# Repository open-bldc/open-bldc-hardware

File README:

This project aims to create a fully open-source Brushless Drive Controller.

This repository contains all current and past hardware designs. Please refer to the open-bldc repository for the source code.

Licensing
---------
All sourcecode is licensed under GPL version 3 or later, all circuitry designs
and pcb layouts are available as original source files and licensed under
CreativeCommons BY-SA 3.0.

Feel free to use everything here as you wish! :)

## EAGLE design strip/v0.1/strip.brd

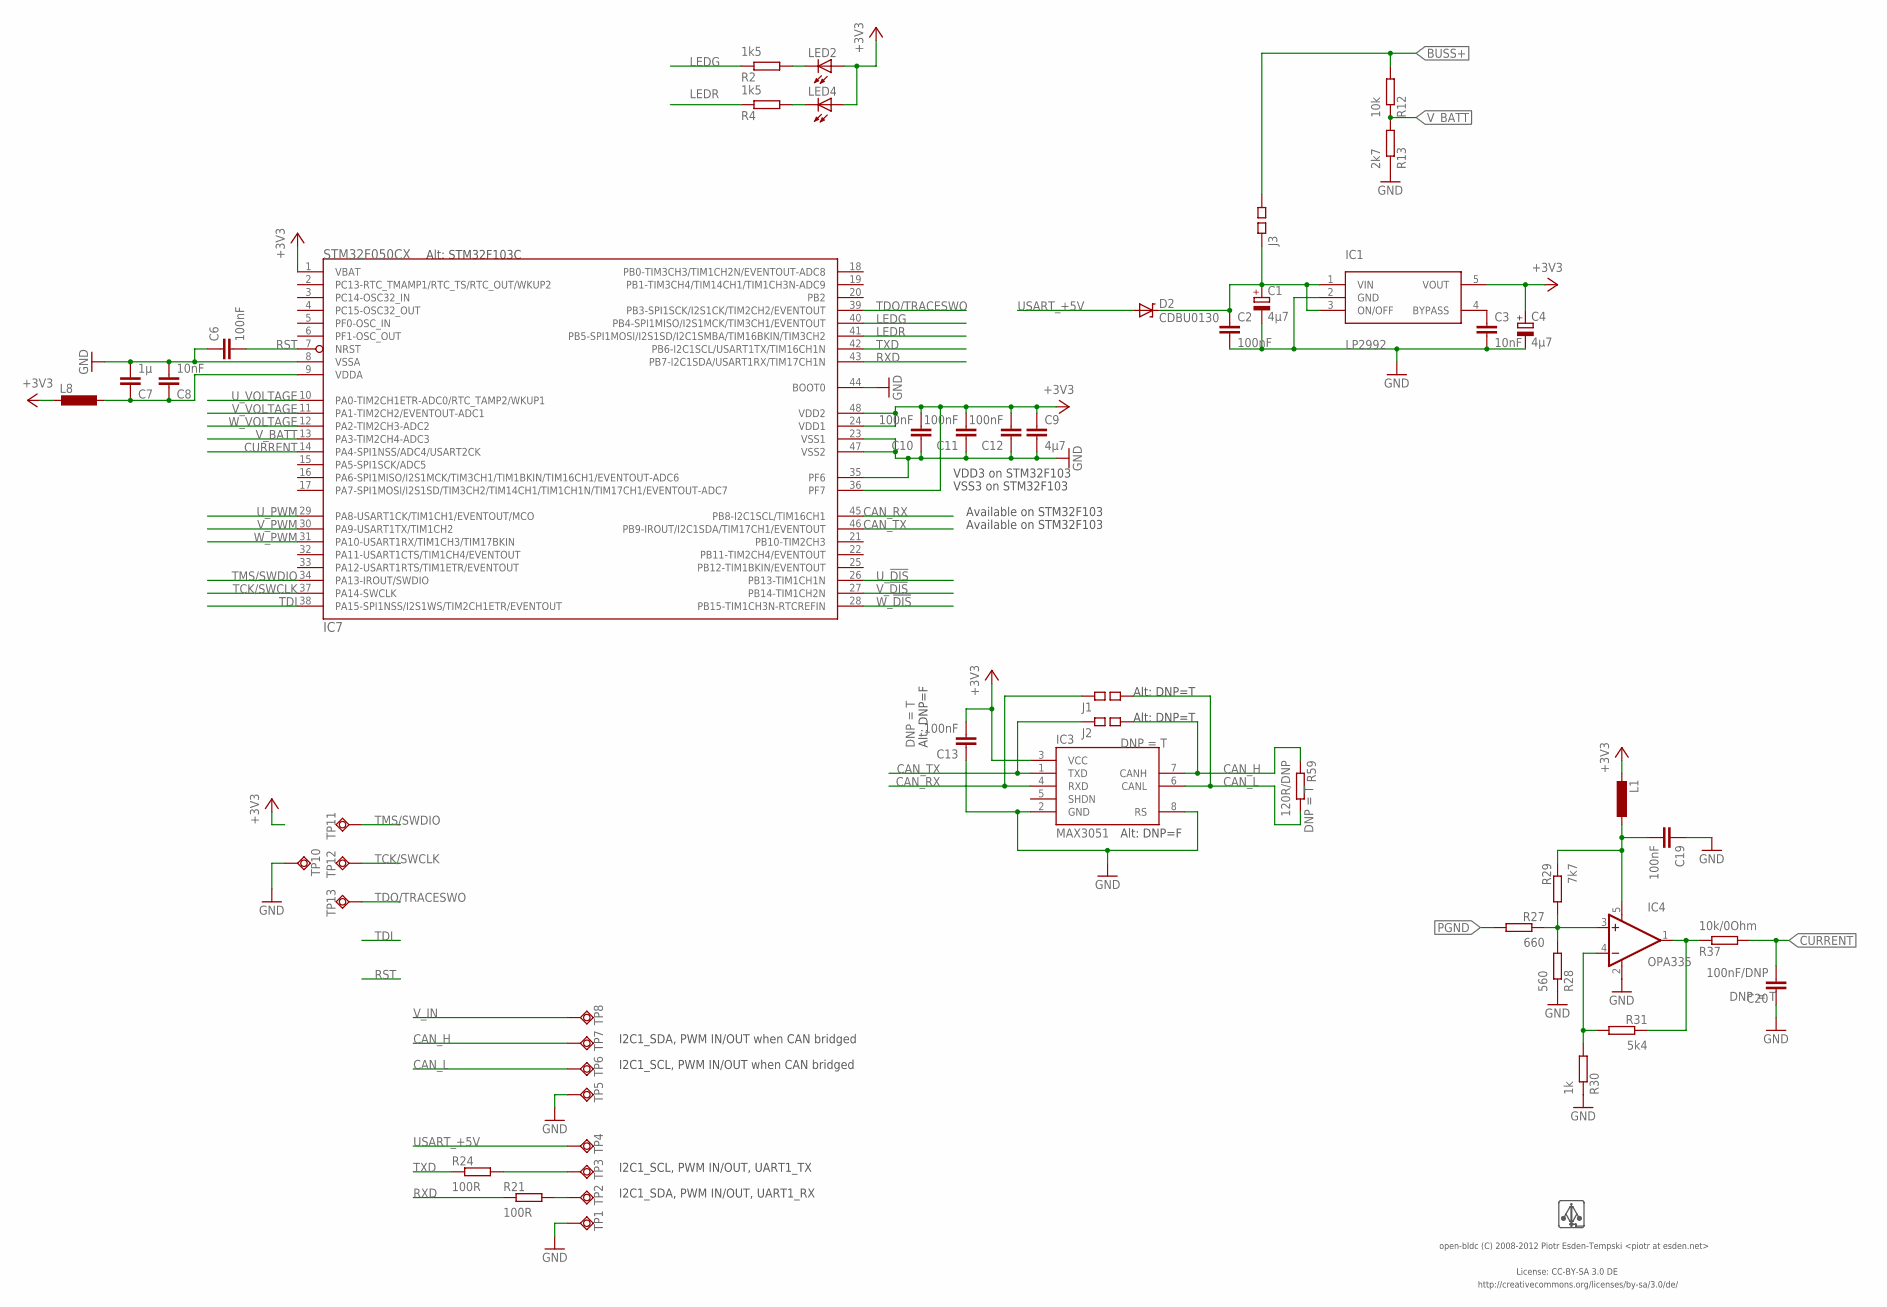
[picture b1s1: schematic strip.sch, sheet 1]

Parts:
C1, C4: 4µ7; 0805-POL-CAP; PARTNO cap-cer-0805-4u7-16v
C2, C6, C10, C11, C12, C13, C19: 100nF; 0402-CAP; PARTNO cap-cer-0402-100n
C3, C8: 10nF; 0402-CAP; PARTNO cap-cer-0402-10n
C7: 1µ; 0402-CAP; PARTNO cap-cer-0402-1u
C9: 4µ7; 0805-CAP; PARTNO cap-cer-0805-4u7
C20: 100nF/DNP; 0402-CAP; PARTNO cap-cer-0402-100n
D2: CDBU0130; 0603-DIO; PARTNO diode-0603
IC1: LP2992; SOT23-5; PARTNO vreg-sot-23-5-3v3
IC3: MAX3051; SO8; PARTNO ic-so8-can-3v3
IC4: OPA335; SOT23-5; PARTNO ic-sot-23-5-opamp
IC7: STM32F050CX; LQFP48; PARTNO mcu-lqfp-48-stm32f05
J1, J2, J3: SQ_JMP-0402; 0402-SQJMP; PARTNO res-0402-0
L1, L8: INDUCTOR-0603; 0603-IND; PARTNO ferrite-0603-600ohm
LED2: GREEN; 0402-LED; PARTNO led-0402-green
LED4: RED; 0402-LED; PARTNO led-0402-green
R2, R4: 1k5; 0402-RES; PARTNO res-0402-1k5
R12: 10k; 0402-RES; PARTNO res-0402-10k
R13: 2k7; 0402-RES; PARTNO res-0402-2k7
R21, R24: 100R; 0402-RES; PARTNO res-0402-100
R27: 660; 0402-RES; PARTNO res-0402-665
R28: 560; 0402-RES; PARTNO res-0402-560
R29: 7k7; 0402-RES; PARTNO res-0402-7k68
R30: 1k; 0402-RES; PARTNO res-0402-1k
R31: 5k4; 0402-RES; PARTNO res-0402-5k36
R37: 10k/0Ohm; 0402-RES; PARTNO res-0402-0
R59: 120R/DNP; 0402-RES; PARTNO res-0402-60.4
TP1, TP2, TP3, TP4, TP5, TP6, TP7, TP8: TPSQTP20SQ; TP20SQ; PARTNO *
TP10, TP11, TP12, TP13: TPSQTP11SQ; TP11SQ; PARTNO *
U$1: LOGO; LOGO_SILK_SMALL; PARTNO *

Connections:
+3V3: C4.+, C9.P$1 (1), C10.P$2 (2), C11.P$2 (2), C12.P$2 (2), C13.P$2 (2), IC1.5 (VOUT), IC3.3 (VCC), IC7.1 (VBAT), IC7.24 (VDD1), IC7.36 (PF7), IC7.48 (VDD2), L1.P$2 (2), L8.P$2 (2), LED2.A, LED4.A
BUSS+: J3.P$2 (2), R12.P$2 (2); also elsewhere on the board
CAN_H: IC3.7 (CANH), J2.P$2 (2), R59.P$1 (1), TP7.TP
CAN_L: IC3.6 (CANL), J1.P$2 (2), R59.P$2 (2), TP6.TP
CAN_RX: IC3.4 (RXD), IC7.45 (PB8-I2C1SCL/TIM16CH1), J1.P$1 (1)
CAN_TX: IC3.1 (TXD), IC7.46 (PB9-IROUT/I2C1SDA/TIM17CH1/EVENTOUT), J2.P$1 (1)
CURRENT: C20.P$2 (2), IC7.14 (PA4-SPI1NSS/ADC4/USART2CK), R37.P$2 (2)
CURRENT_RAW: IC4.1 (OUT), R31.P$1 (1), R37.P$1 (1)
GND: C1.-, C2.P$2 (2), C3.P$2 (2), C4.-, C6.P$1 (1), C7.P$2 (2), C8.P$2 (2), C9.P$2 (2), C10.P$1 (1), C11.P$1 (1), C12.P$1 (1), C13.P$1 (1), C19.P$1 (1), C20.P$1 (1), IC1.2 (GND), IC3.2 (GND), IC3.8 (RS), IC4.2 (V-), IC7.8 (VSSA), IC7.23 (VSS1), IC7.35 (PF6), IC7.44 (BOOT0), IC7.47 (VSS2), R13.P$1 (1), R28.P$1 (1), R30.P$1 (1), TP1.TP, TP5.TP, TP10.TP; also elsewhere on the board
LEDG: IC7.40 (PB4-SPI1MISO/I2S1MCK/TIM3CH1/EVENTOUT), R2.P$1 (1)
LEDR: IC7.41 (PB5-SPI1MOSI/I2S1SD/I2C1SMBA/TIM16BKIN/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), R4.P$1 (1)
unnamed: LED4.C, R4.P$2 (2)
unnamed: R21.P$2 (2), TP2.TP
unnamed: C19.P$2 (2), IC4.5 (V+), L1.P$1 (1), R29.P$1 (1)
unnamed: LED2.C, R2.P$2 (2)
unnamed: IC4.3 (+IN), R27.P$1 (1), R28.P$2 (2), R29.P$2 (2)
unnamed: IC4.4 (-IN), R30.P$2 (2), R31.P$2 (2)
unnamed: R24.P$2 (2), TP3.TP
unnamed: C3.P$1 (1), IC1.4 (BYPASS)
PGND: R27.P$2 (2); also elsewhere on the board
RST: C6.P$2 (2), IC7.7 (NRST)
RXD: IC7.43 (PB7-I2C1SDA/USART1RX/TIM17CH1N), R21.P$1 (1)
TCK/SWCLK: IC7.37 (PA14-SWCLK), TP12.TP
TDI: IC7.38 (PA15-SPI1NSS/I2S1WS/TIM2CH1ETR/EVENTOUT)
TDO/TRACESWO: IC7.39 (PB3-SPI1SCK/I2S1CK/TIM2CH2/EVENTOUT), TP13.TP
TMS/SWDIO: IC7.34 (PA13-IROUT/SWDIO), TP11.TP
TXD: IC7.42 (PB6-I2C1SCL/USART1TX/TIM16CH1N), R24.P$1 (1)
USART_+5V: D2.A, TP4.TP
U_!DIS: IC7.26 (PB13-TIM1CH1N); also elsewhere on the board
U_PWM: IC7.29 (PA8-USART1CK/TIM1CH1/EVENTOUT/MCO); also elsewhere on the board
U_VOLTAGE: IC7.10 (PA0-TIM2CH1ETR-ADC0/RTC_TAMP2/WKUP1); also elsewhere on the board
VDDA: C7.P$1 (1), C8.P$1 (1), IC7.9 (VDDA), L8.P$1 (1)
V_!DIS: IC7.27 (PB14-TIM1CH2N); also elsewhere on the board
V_BATT: IC7.13 (PA3-TIM2CH4-ADC3), R12.P$1 (1), R13.P$2 (2)
V_IN: C1.+, C2.P$1 (1), D2.C, IC1.1 (VIN), IC1.3 (ON/OFF), J3.P$1 (1), TP8.TP
V_PWM: IC7.30 (PA9-USART1TX/TIM1CH2); also elsewhere on the board
V_VOLTAGE: IC7.11 (PA1-TIM2CH2/EVENTOUT-ADC1); also elsewhere on the board
W_!DIS: IC7.28 (PB15-TIM1CH3N-RTCREFIN); also elsewhere on the board
W_PWM: IC7.31 (PA10-USART1RX/TIM1CH3/TIM17BKIN); also elsewhere on the board
W_VOLTAGE: IC7.12 (PA2-TIM2CH3-ADC2); also elsewhere on the board

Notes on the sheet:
License: CC-BY-SA 3.0 DE
http://creativecommons.org/licenses/by-sa/3.0/de/
open-bldc (C) 2008-2012 Piotr Esden-Tempski <piotr at esden.net>
VDD3 on STM32F103
VSS3 on STM32F103
Available on STM32F103
Alt: STM32F103C
Alt: DNP=T
Alt: DNP=F
I2C1_SDA, PWM IN/OUT when CAN bridged
I2C1_SCL, PWM IN/OUT when CAN bridged
I2C1_SCL, PWM IN/OUT, UART1_TX
I2C1_SDA, PWM IN/OUT, UART1_RX

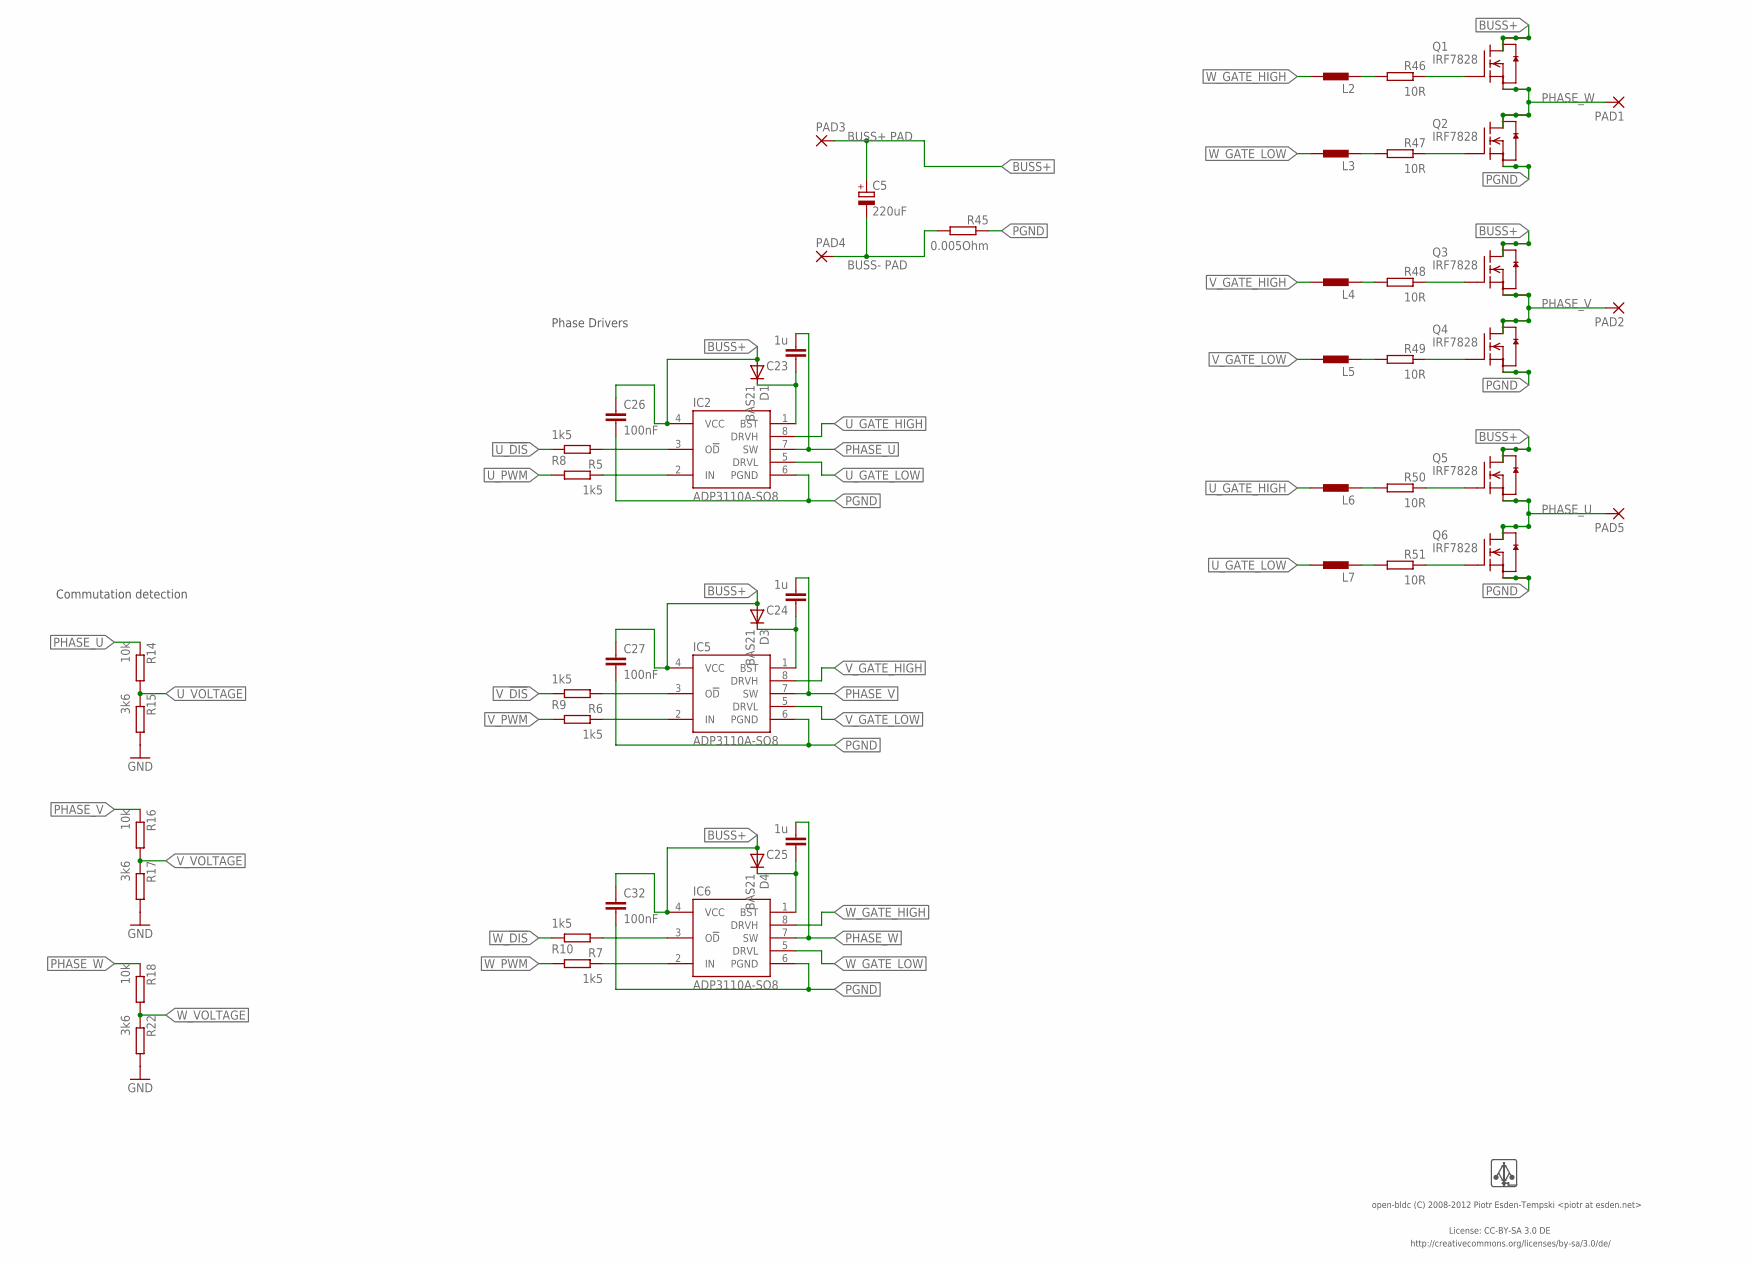
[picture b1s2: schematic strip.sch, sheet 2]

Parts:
C5: 220uF; 7343/D; PARTNO cap-tan-D-220u-16v
C23, C24, C25: 1u; 0603-CAP; PARTNO cap-tan-0603-1u
C26, C27, C32: 100nF; 0402-CAP; PARTNO cap-cer-0402-100n
D1, D3, D4: BAS21; SOD-123-DIO; PARTNO diode-sod-123
IC2, IC5, IC6: ADP3110A-SO8; SO8; PARTNO ic-so8-mosfet-driver-buck
L2, L3, L4, L5, L6, L7: INDUCTOR-0402; 0402-IND; PARTNO res-0402-0
PAD1, PAD2, PAD3, PAD4, PAD5: SMD5; SMD2,54-5,08; PARTNO *
Q1, Q2, Q3, Q4, Q5, Q6: IRF7828; SO8; PARTNO ic-so8-mosfet-n-ch-30v-15a
R5, R6, R7, R8, R9, R10: 1k5; 0402-RES; PARTNO res-0402-1k5
R14, R16, R18: 10k; 0402-RES; PARTNO res-0402-10k
R15, R17, R22: 3k6; 0402-RES; PARTNO res-0402-3k6
R45: 0.005Ohm; 1206-RES; PARTNO res-1206-0005
R46, R47, R48, R49, R50, R51: 10R; 0402-RES; PARTNO res-0402-10
U$2: LOGO; LOGO_SILK_SMALL; PARTNO *

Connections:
BUSS+: C5.+, C26.P$1 (1), C27.P$1 (1), C32.P$1 (1), D1.A, D3.A, D4.A, IC2.4 (VCC), IC5.4 (VCC), IC6.4 (VCC), PAD3.1, Q1.5 (D1), Q1.6 (D2), Q1.7 (D3), Q1.8 (D4), Q3.5 (D1), Q3.6 (D2), Q3.7 (D3), Q3.8 (D4), Q5.5 (D1), Q5.6 (D2), Q5.7 (D3), Q5.8 (D4); also elsewhere on the board
GND: C5.-, PAD4.1, R15.P$2 (2), R17.P$2 (2), R22.P$2 (2), R45.P$2 (2); also elsewhere on the board
unnamed: C23.P$1 (1), D1.C, IC2.1 (BST)
unnamed: C24.P$1 (1), D3.C, IC5.1 (BST)
unnamed: C25.P$1 (1), D4.C, IC6.1 (BST)
unnamed: L2.P$2 (2), R46.P$2 (2)
unnamed: L3.P$2 (2), R47.P$2 (2)
unnamed: L4.P$2 (2), R48.P$2 (2)
unnamed: L5.P$2 (2), R49.P$2 (2)
unnamed: L6.P$2 (2), R50.P$2 (2)
unnamed: L7.P$2 (2), R51.P$2 (2)
unnamed: Q1.4 (G), R46.P$1 (1)
unnamed: Q2.4 (G), R47.P$1 (1)
unnamed: Q3.4 (G), R48.P$1 (1)
unnamed: Q4.4 (G), R49.P$1 (1)
unnamed: Q5.4 (G), R50.P$1 (1)
unnamed: Q6.4 (G), R51.P$1 (1)
PGND: C26.P$2 (2), C27.P$2 (2), C32.P$2 (2), IC2.6 (PGND), IC5.6 (PGND), IC6.6 (PGND), Q2.1 (S3), Q2.2 (S2), Q2.3 (S1), Q4.1 (S3), Q4.2 (S2), Q4.3 (S1), Q6.1 (S3), Q6.2 (S2), Q6.3 (S1), R45.P$1 (1); also elsewhere on the board
PHASE_U: C23.P$2 (2), IC2.7 (SW), PAD5.1, Q5.1 (S3), Q5.2 (S2), Q5.3 (S1), Q6.5 (D1), Q6.6 (D2), Q6.7 (D3), Q6.8 (D4), R14.P$1 (1)
PHASE_V: C24.P$2 (2), IC5.7 (SW), PAD2.1, Q3.1 (S3), Q3.2 (S2), Q3.3 (S1), Q4.5 (D1), Q4.6 (D2), Q4.7 (D3), Q4.8 (D4), R16.P$1 (1)
PHASE_W: C25.P$2 (2), IC6.7 (SW), PAD1.1, Q1.1 (S3), Q1.2 (S2), Q1.3 (S1), Q2.5 (D1), Q2.6 (D2), Q2.7 (D3), Q2.8 (D4), R18.P$1 (1)
U_!DIS: R8.P$1 (1); also elsewhere on the board
U_!DIS!1: IC2.3 (O!D), R8.P$2 (2)
U_GATE_HIGH: IC2.8 (DRVH), L6.P$1 (1)
U_GATE_LOW: IC2.5 (DRVL), L7.P$1 (1)
U_PWM: R5.P$2 (2); also elsewhere on the board
U_PWM1: IC2.2 (IN), R5.P$1 (1)
U_VOLTAGE: R14.P$2 (2), R15.P$1 (1); also elsewhere on the board
V_!DIS: R9.P$1 (1); also elsewhere on the board
V_!DIS!1: IC5.3 (O!D), R9.P$2 (2)
V_GATE_HIGH: IC5.8 (DRVH), L4.P$1 (1)
V_GATE_LOW: IC5.5 (DRVL), L5.P$1 (1)
V_PWM: R6.P$2 (2); also elsewhere on the board
V_PWM1: IC5.2 (IN), R6.P$1 (1)
V_VOLTAGE: R16.P$2 (2), R17.P$1 (1); also elsewhere on the board
W_!DIS: R10.P$1 (1); also elsewhere on the board
W_!DIS1: IC6.3 (O!D), R10.P$2 (2)
W_GATE_HIGH: IC6.8 (DRVH), L2.P$1 (1)
W_GATE_LOW: IC6.5 (DRVL), L3.P$1 (1)
W_PWM: R7.P$2 (2); also elsewhere on the board
W_PWM1: IC6.2 (IN), R7.P$1 (1)
W_VOLTAGE: R18.P$2 (2), R22.P$1 (1); also elsewhere on the board

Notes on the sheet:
Phase Drivers
Commutation detection
BUSS+ PAD
BUSS- PAD
License: CC-BY-SA 3.0 DE
http://creativecommons.org/licenses/by-sa/3.0/de/
open-bldc (C) 2008-2012 Piotr Esden-Tempski <piotr at esden.net>

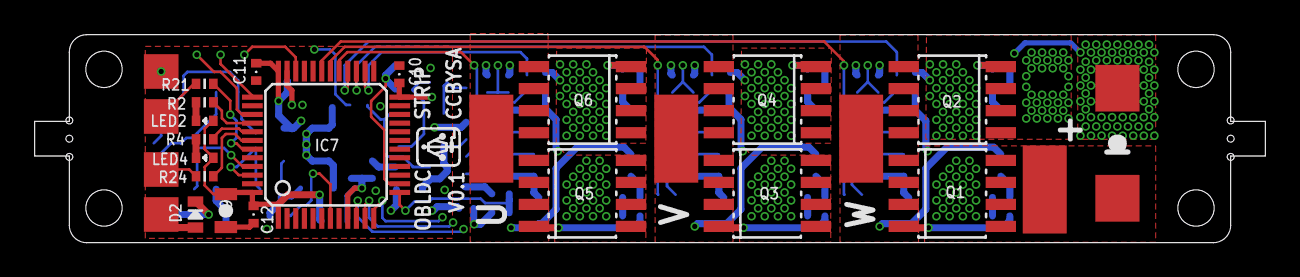
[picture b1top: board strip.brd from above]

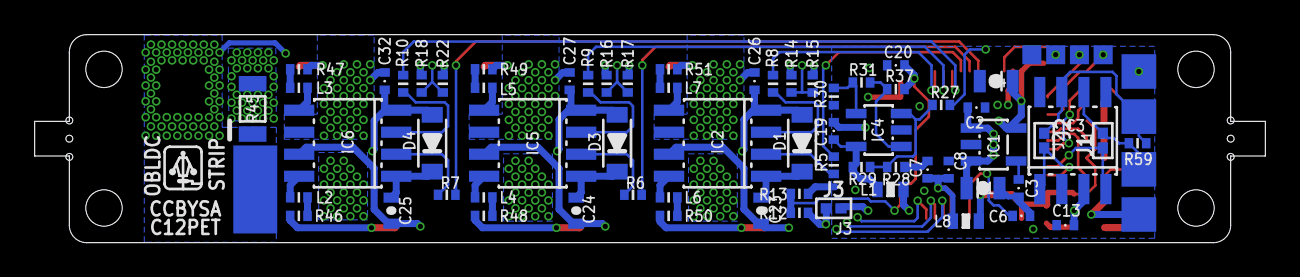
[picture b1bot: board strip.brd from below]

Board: 4 copper layers, 71.0 x 12.0 mm, 102 parts (74 on the bottom side), 69 nets.

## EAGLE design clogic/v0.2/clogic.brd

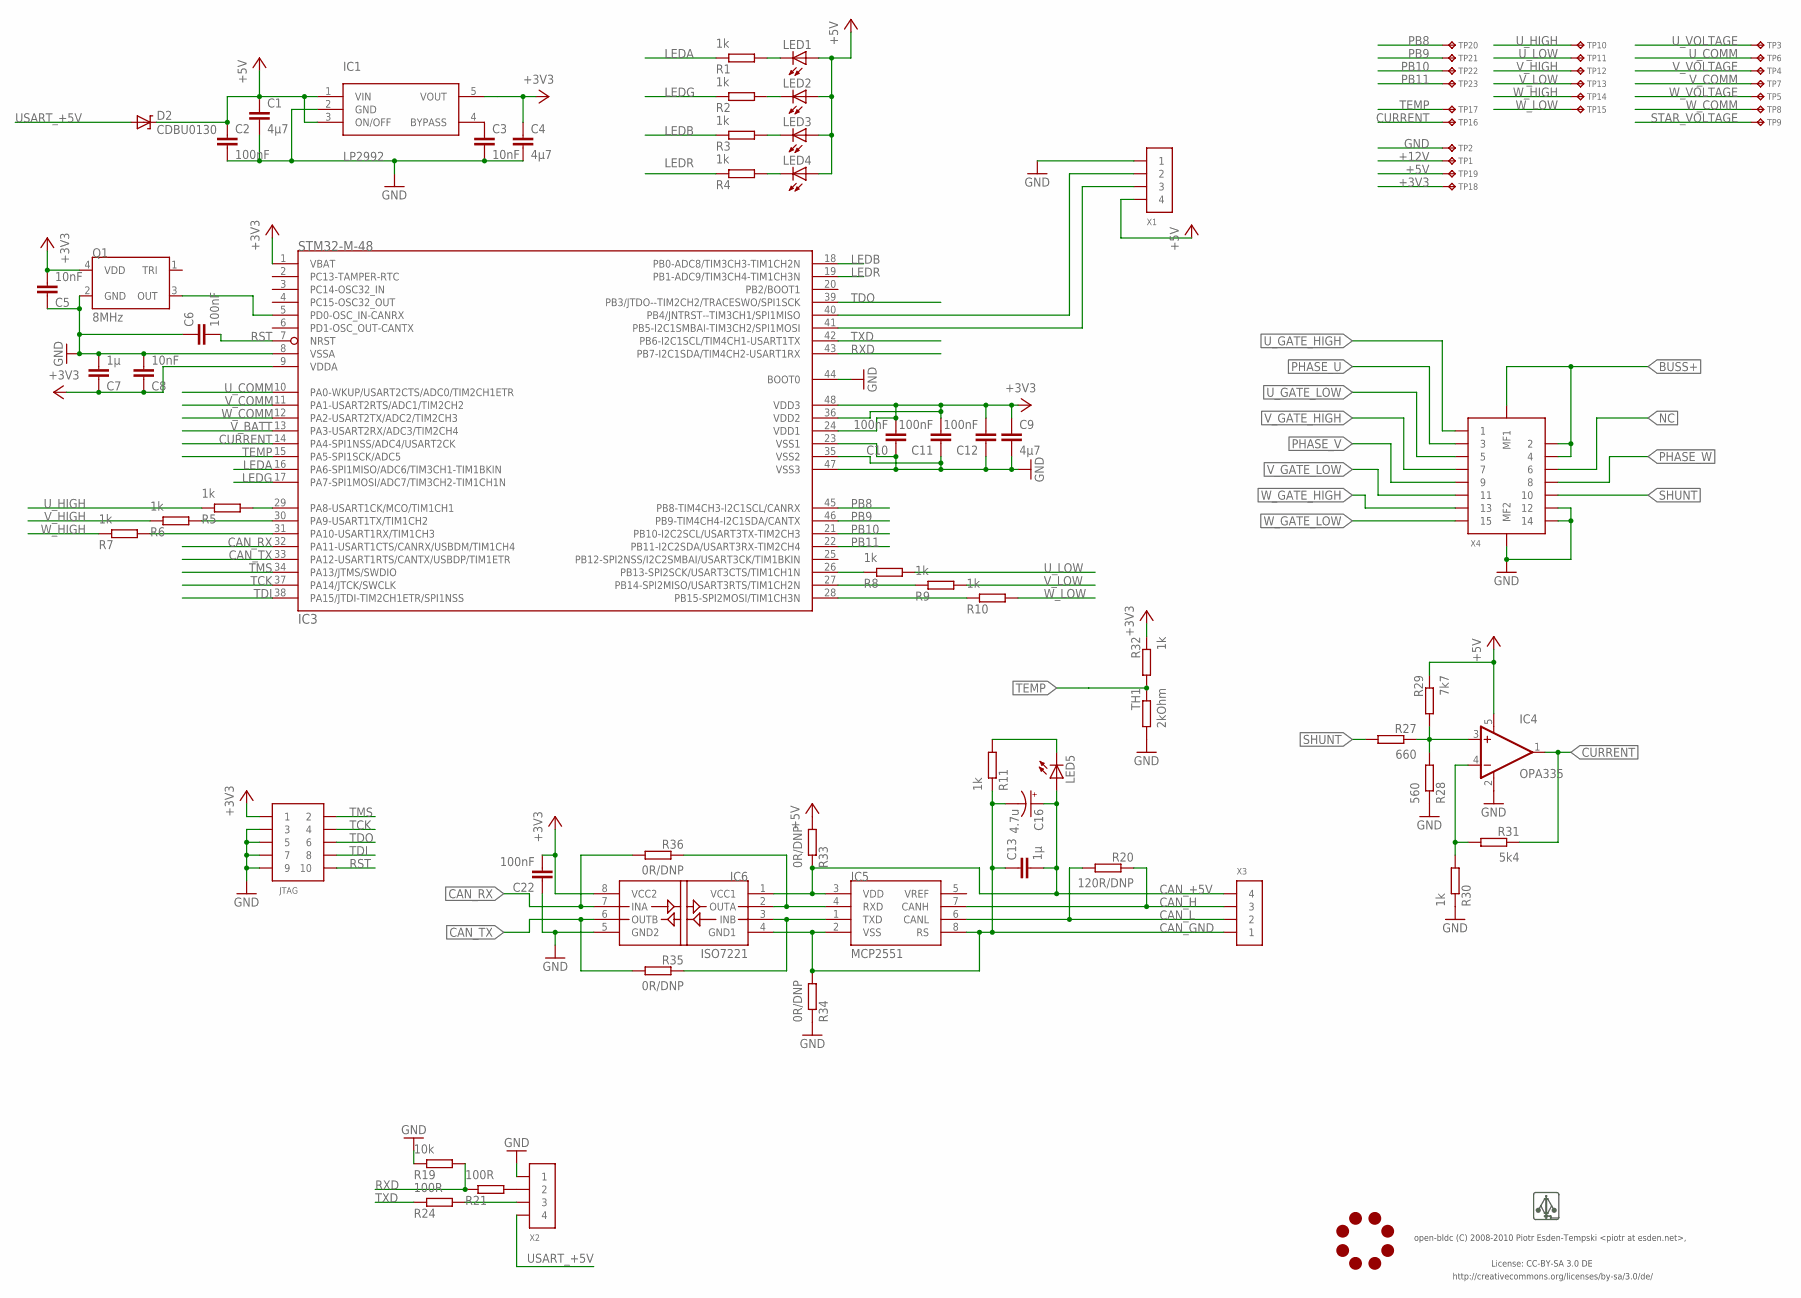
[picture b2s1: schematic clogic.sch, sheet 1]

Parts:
C1, C4, C9: 4µ7; 0603-CAP
C2, C6, C10, C11, C12, C22: 100nF; 0603-CAP
C3, C5, C8: 10nF; 0603-CAP
C7, C13: 1µ; 0603-CAP
C16: 4.7u; CAP_0805TANT_F95
D2: CDBU0130; 0603-LED
IC1: LP2992; SOT23-5
IC3: STM32-M-48; LQFP48
IC4: OPA335; SOT23-5
IC5: MCP2551; SO8
IC6: ISO7221; SO8
JL1: JOBY_LOGO-6MIL; JOBY_LOGO_6MIL
JTAG: CONN_5-2-FTSH-V; FTSH-105-DV
LED1: AMBER; 0603-LED
LED2: GREEN; 0603-LED
LED3: BLUE; 0603-LED
LED4: RED; 0603-LED
LED5: WHITE; 0603-LED
Q1: 8MHz; ASE_OSCILLATOR
R1, R2, R3, R4, R5, R6, R7, R8, R9, R10, R11, R30, R32: 1k; 0603-RES
R19: 10k; 0603-RES
R20: 120R/DNP; 0603-RES
R21, R24: 100R; 0603-RES
R27: 660; 0603-RES
R28: 560; 0603-RES
R29: 7k7; 0603-RES
R31: 5k4; 0603-RES
R33, R34, R35, R36: 0R/DNP; 0603-RES
TH1: 2kOhm; 0603-RES
TP1, TP2, TP3, TP4, TP5, TP6, TP7, TP8, TP9, TP10, TP11, TP12, TP13, TP14, TP15, TP16, TP17, TP18, TP19, TP20, TP21, TP22, TP23: TP-09RSMD; TP09R
U$1: LOGO
X1, X2, X3: CONN_4-1-53261; PB-53261-04
X4: CONN_15-2-2MT-DF9; DF9-15

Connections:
+3V3: C4.P$1 (1), C5.P$2 (2), C7.P$1 (1), C8.P$1 (1), C9.P$1 (1), C10.P$2 (2), C11.P$2 (2), C12.P$2 (2), C22.P$2 (2), IC1.5 (VOUT), IC3.1 (VBAT), IC3.9 (VDDA), IC3.24 (VDD1), IC3.36 (VDD2), IC3.48 (VDD3), IC6.8 (VCC2), JTAG.1, Q1.4 (VDD), R32.P$1 (1), TP18.P$1
+5V: C1.P$1 (1), C2.P$1 (1), D2.C, IC1.1 (VIN), IC1.3 (ON/OFF), IC4.5 (V+), LED1.A, LED2.A, LED3.A, LED4.A, R29.P$1 (1), R33.P$2 (2), TP19.P$1, X1.4; also elsewhere on the board
+12V: TP1.P$1; also elsewhere on the board
A: IC3.40 (PB4/JNTRST--TIM3CH1/SPI1MISO), X1.2
B: IC3.41 (PB5-I2C1SMBAI-TIM3CH2/SPI1MOSI), X1.3
BUSS+: X4.2, X4.4, X4.MF1; also elsewhere on the board
CAN_+5V: C13.P$2 (2), C16.P$1 (+), IC5.3 (VDD), IC6.1 (VCC1), LED5.A, R33.P$1 (1), X3.4
CAN_GND: C13.P$1 (1), C16.P$2 (-), IC5.2 (VSS), IC5.8 (RS), IC6.4 (GND1), R11.P$1 (1), R34.P$2 (2), X3.1
CAN_H: IC5.7 (CANH), R20.P$1 (1), X3.3
CAN_L: IC5.6 (CANL), R20.P$2 (2), X3.2
CAN_RX: IC3.32 (PA11-USART1CTS/CANRX/USBDM/TIM1CH4), IC6.7 (INA), R36.P$2 (2)
CAN_TX: IC3.33 (PA12-USART1RTS/CANTX/USBDP/TIM1ETR), IC6.6 (OUTB), R35.P$2 (2)
CURRENT: IC3.14 (PA4-SPI1NSS/ADC4/USART2CK), IC4.1 (OUT), R31.P$1 (1), TP16.P$1
GND: C1.P$2 (2), C2.P$2 (2), C3.P$2 (2), C4.P$2 (2), C5.P$1 (1), C6.P$1 (1), C7.P$2 (2), C8.P$2 (2), C9.P$2 (2), C10.P$1 (1), C11.P$1 (1), C12.P$1 (1), C22.P$1 (1), IC1.2 (GND), IC3.8 (VSSA), IC3.23 (VSS1), IC3.35 (VSS2), IC3.44 (BOOT0), IC3.47 (VSS3), IC4.2 (V-), IC6.5 (GND2), JTAG.3, JTAG.5, JTAG.7, JTAG.9, Q1.2 (GND), R19.P$1 (1), R28.P$1 (1), R30.P$1 (1), R34.P$1 (1), TH1.P$2 (2), TP2.P$1, X1.1, X2.1, X4.12, X4.14, X4.MF2; also elsewhere on the board
LEDA: IC3.16 (PA6-SPI1MISO/ADC6/TIM3CH1-TIM1BKIN), R1.P$1 (1)
LEDB: IC3.18 (PB0-ADC8/TIM3CH3-TIM1CH2N), R3.P$1 (1)
LEDG: IC3.17 (PA7-SPI1MOSI/ADC7/TIM3CH2-TIM1CH1N), R2.P$1 (1)
LEDR: IC3.19 (PB1-ADC9/TIM3CH4-TIM1CH3N), R4.P$1 (1)
unnamed: LED5.C, R11.P$2 (2)
unnamed: LED1.C, R1.P$2 (2)
unnamed: LED4.C, R4.P$2 (2)
unnamed: LED3.C, R3.P$2 (2)
unnamed: R21.P$2 (2), X2.2
unnamed: LED2.C, R2.P$2 (2)
unnamed: IC4.3 (+IN), R27.P$1 (1), R28.P$2 (2), R29.P$2 (2)
unnamed: IC4.4 (-IN), R30.P$2 (2), R31.P$2 (2)
unnamed: IC5.1 (TXD), IC6.3 (INB), R35.P$1 (1)
unnamed: IC5.4 (RXD), IC6.2 (OUTA), R36.P$1 (1)
unnamed: R24.P$2 (2), X2.3
unnamed: C3.P$1 (1), IC1.4 (BYPASS)
unnamed: IC3.26 (PB13-SPI2SCK/USART3CTS/TIM1CH1N), R8.P$1 (1)
unnamed: IC3.27 (PB14-SPI2MISO/USART3RTS/TIM1CH2N), R9.P$1 (1)
unnamed: IC3.28 (PB15-SPI2MOSI/TIM1CH3N), R10.P$1 (1)
unnamed: IC3.5 (PD0-OSC_IN-CANRX), Q1.3 (OUT)
unnamed: IC3.29 (PA8-USART1CK/MCO/TIM1CH1), R5.P$2 (2)
unnamed: IC3.30 (PA9-USART1TX/TIM1CH2), R6.P$2 (2)
unnamed: IC3.31 (PA10-USART1RX/TIM1CH3), R7.P$2 (2)
NC: X4.6
PB8: IC3.45 (PB8-TIM4CH3-I2C1SCL/CANRX), TP20.P$1
PB9: IC3.46 (PB9-TIM4CH4-I2C1SDA/CANTX), TP21.P$1
PB10: IC3.21 (PB10-I2C2SCL/USART3TX-TIM2CH3), TP22.P$1
PB11: IC3.22 (PB11-I2C2SDA/USART3RX-TIM2CH4), TP23.P$1
PHASE_U: X4.3; also elsewhere on the board
PHASE_V: X4.9; also elsewhere on the board
PHASE_W: X4.8; also elsewhere on the board
RST: C6.P$2 (2), IC3.7 (NRST), JTAG.10
RXD: IC3.43 (PB7-I2C1SDA/TIM4CH2-USART1RX), R19.P$2 (2), R21.P$1 (1)
SHUNT: R27.P$2 (2), X4.10
STAR_VOLTAGE: TP9.P$1; also elsewhere on the board
TCK: IC3.37 (PA14/JTCK/SWCLK), JTAG.4
TDI: IC3.38 (PA15/JTDI-TIM2CH1ETR/SPI1NSS), JTAG.8
TDO: IC3.39 (PB3/JTDO--TIM2CH2/TRACESWO/SPI1SCK), JTAG.6
TEMP: IC3.15 (PA5-SPI1SCK/ADC5), R32.P$2 (2), TH1.P$1 (1), TP17.P$1
TMS: IC3.34 (PA13/JTMS/SWDIO), JTAG.2
TXD: IC3.42 (PB6-I2C1SCL/TIM4CH1-USART1TX), R24.P$1 (1)
USART_+5V: D2.A, X2.4
U_COMM: IC3.10 (PA0-WKUP/USART2CTS/ADC0/TIM2CH1ETR), TP6.P$1; also elsewhere on the board
U_GATE_HIGH: X4.1; also elsewhere on the board
U_GATE_LOW: X4.5; also elsewhere on the board
U_HIGH: R5.P$1 (1), TP10.P$1; also elsewhere on the board
U_LOW: R8.P$2 (2), TP11.P$1; also elsewhere on the board
U_VOLTAGE: TP3.P$1; also elsewhere on the board
V_BATT: IC3.13 (PA3-USART2RX/ADC3/TIM2CH4); also elsewhere on the board
V_COMM: IC3.11 (PA1-USART2RTS/ADC1/TIM2CH2), TP7.P$1; also elsewhere on the board
V_GATE_HIGH: X4.7; also elsewhere on the board
V_GATE_LOW: X4.11; also elsewhere on the board
V_HIGH: R6.P$1 (1), TP12.P$1; also elsewhere on the board
V_LOW: R9.P$2 (2), TP13.P$1; also elsewhere on the board
V_VOLTAGE: TP4.P$1; also elsewhere on the board
W_COMM: IC3.12 (PA2-USART2TX/ADC2/TIM2CH3), TP8.P$1; also elsewhere on the board
W_GATE_HIGH: X4.13; also elsewhere on the board
W_GATE_LOW: X4.15; also elsewhere on the board
W_HIGH: R7.P$1 (1), TP14.P$1; also elsewhere on the board
W_LOW: R10.P$2 (2), TP15.P$1; also elsewhere on the board
W_VOLTAGE: TP5.P$1; also elsewhere on the board

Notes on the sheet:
License: CC-BY-SA 3.0 DE
http://creativecommons.org/licenses/by-sa/3.0/de/
open-bldc (C) 2008-2010 Piotr Esden-Tempski <piotr at esden.net>,

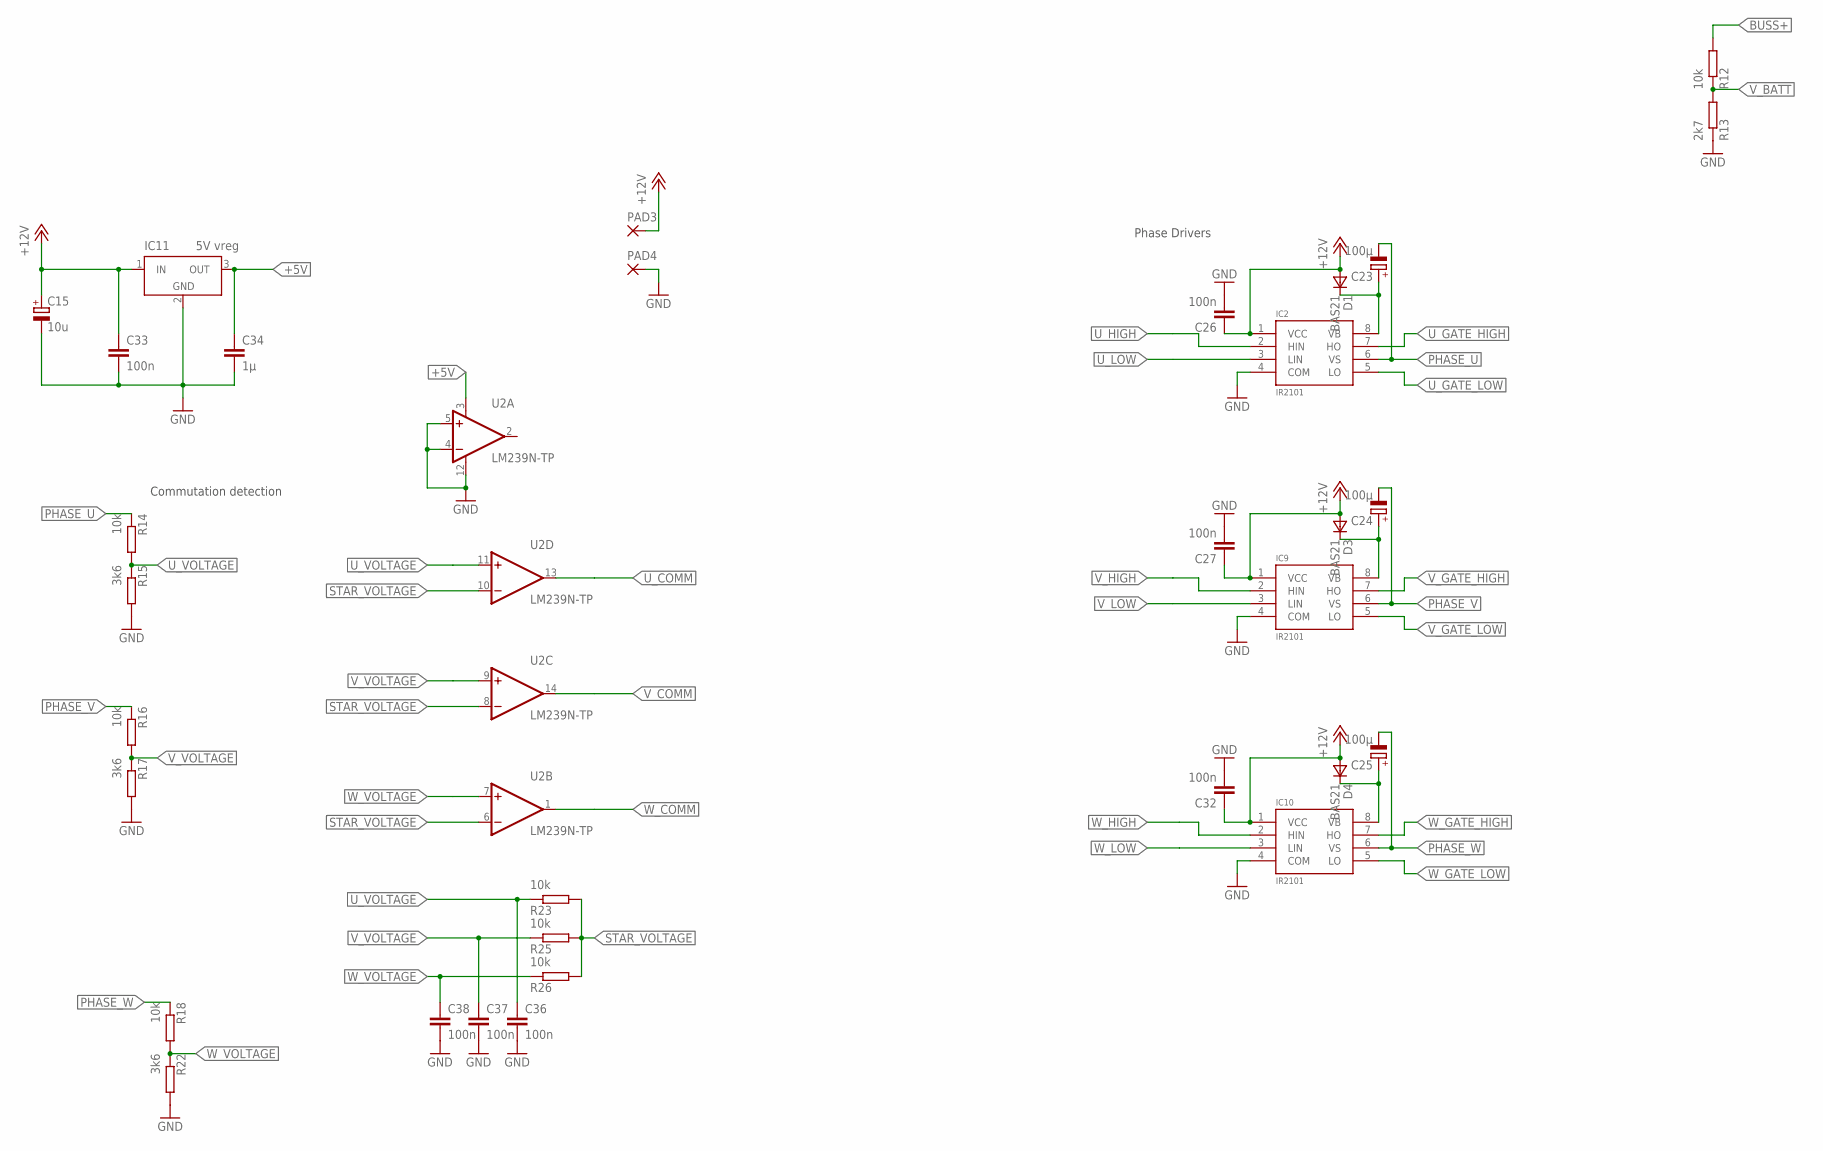
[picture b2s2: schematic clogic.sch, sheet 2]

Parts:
C15: 10u; 3528/B
C23, C24, C25: 100µ; 0805-POL-CAP
C26, C27, C32, C33, C36, C37, C38: 100n; 0603-CAP
C34: 1µ; 0603-CAP
D1, D3, D4: BAS21; SOT-23
IC2, IC9, IC10: IR2101; SO-8
IC11: 5V vreg; SOT223
PAD3, PAD4: SMD5; SMD2,54-5,08
R12, R14, R16, R18, R23, R25, R26: 10k; 0603-RES
R13: 2k7; 0603-RES
R15, R17, R22: 3k6; 0603-RES
U2: LM239N-TP; TSSOP_14

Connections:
+5V: C34.P$1 (1), IC11.3 (OUT), U2.3 (V+); also elsewhere on the board
+12V: C15.+, C26.P$1 (1), C27.P$1 (1), C32.P$1 (1), C33.P$1 (1), D1.3 (A), D3.3 (A), D4.3 (A), IC2.1 (VCC), IC9.1 (VCC), IC10.1 (VCC), IC11.1 (IN), PAD3.1; also elsewhere on the board
BUSS+: R12.P$2 (2); also elsewhere on the board
GND: C15.-, C26.P$2 (2), C27.P$2 (2), C32.P$2 (2), C33.P$2 (2), C34.P$2 (2), C36.P$2 (2), C37.P$2 (2), C38.P$2 (2), IC2.4 (COM), IC9.4 (COM), IC10.4 (COM), IC11.2 (GND), IC11.4 (GND), PAD4.1, R13.P$1 (1), R15.P$2 (2), R17.P$2 (2), R22.P$2 (2), U2.4 (-IN), U2.5 (+IN), U2.12 (V-); also elsewhere on the board
unnamed: C23.+, D1.1 (C), IC2.8 (VB)
unnamed: C24.+, D3.1 (C), IC9.8 (VB)
unnamed: C25.+, D4.1 (C), IC10.8 (VB)
PHASE_U: C23.-, IC2.6 (VS), R14.P$1 (1); also elsewhere on the board
PHASE_V: C24.-, IC9.6 (VS), R16.P$1 (1); also elsewhere on the board
PHASE_W: C25.-, IC10.6 (VS), R18.P$1 (1); also elsewhere on the board
STAR_VOLTAGE: R23.P$2 (2), R25.P$2 (2), R26.P$2 (2), U2.6 (-IN), U2.8 (-IN), U2.10 (-IN); also elsewhere on the board
U_COMM: U2.13 (OUT); also elsewhere on the board
U_GATE_HIGH: IC2.7 (HO); also elsewhere on the board
U_GATE_LOW: IC2.5 (LO); also elsewhere on the board
U_HIGH: IC2.2 (HIN); also elsewhere on the board
U_LOW: IC2.3 (LIN); also elsewhere on the board
U_VOLTAGE: C36.P$1 (1), R14.P$2 (2), R15.P$1 (1), R23.P$1 (1), U2.11 (+IN); also elsewhere on the board
V_BATT: R12.P$1 (1), R13.P$2 (2); also elsewhere on the board
V_COMM: U2.14 (OUT); also elsewhere on the board
V_GATE_HIGH: IC9.7 (HO); also elsewhere on the board
V_GATE_LOW: IC9.5 (LO); also elsewhere on the board
V_HIGH: IC9.2 (HIN); also elsewhere on the board
V_LOW: IC9.3 (LIN); also elsewhere on the board
V_VOLTAGE: C37.P$1 (1), R16.P$2 (2), R17.P$1 (1), R25.P$1 (1), U2.9 (+IN); also elsewhere on the board
W_COMM: U2.1 (OUT); also elsewhere on the board
W_GATE_HIGH: IC10.7 (HO); also elsewhere on the board
W_GATE_LOW: IC10.5 (LO); also elsewhere on the board
W_HIGH: IC10.2 (HIN); also elsewhere on the board
W_LOW: IC10.3 (LIN); also elsewhere on the board
W_VOLTAGE: C38.P$1 (1), R18.P$2 (2), R22.P$1 (1), R26.P$1 (1), U2.7 (+IN); also elsewhere on the board

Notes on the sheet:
Phase Drivers
Commutation detection

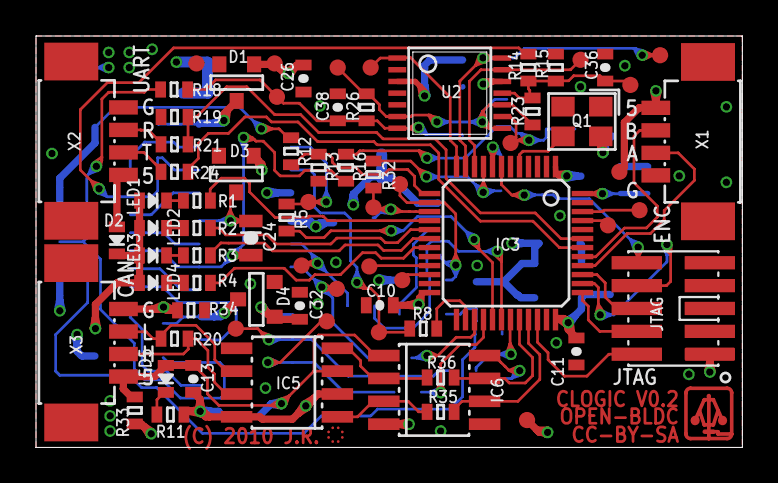
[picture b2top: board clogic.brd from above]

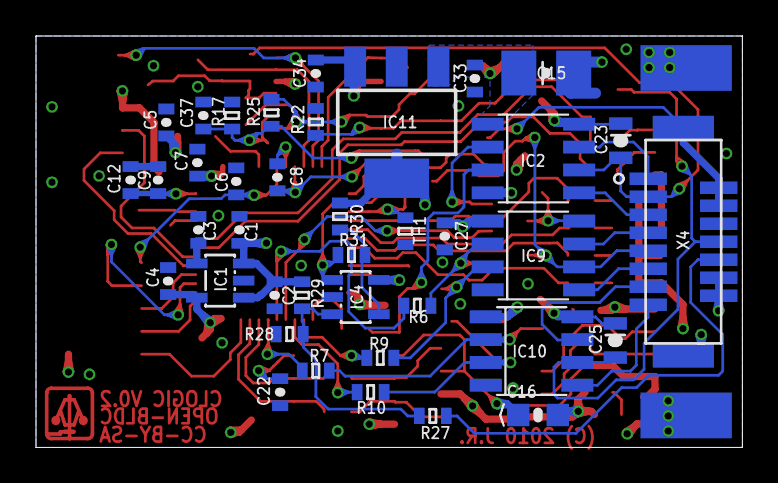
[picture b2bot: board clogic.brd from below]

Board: 4 copper layers, 39.2 x 22.9 mm, 117 parts (41 on the bottom side), 77 nets.

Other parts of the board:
DRILEGEND: DRILEGEND

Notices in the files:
clogic/v0.2/clogic.brd:
(C) 2010 J.R.
discarded/mini/open-bldc.sch:
Creative Commons Attribution - Share Alike 3.0 Germany License
open-blcd mini (C) 2008 Piotr Esden-Tempski
discarded/normal/open-bldc.brd:
open-bldc (C) 2008 Piotr Esden-Tempski
v0.1/power/open-bldc-power.brd:
(C) 2009 ESDEN
v0.3/logic/logic.brd:
(C) 2010 esden
